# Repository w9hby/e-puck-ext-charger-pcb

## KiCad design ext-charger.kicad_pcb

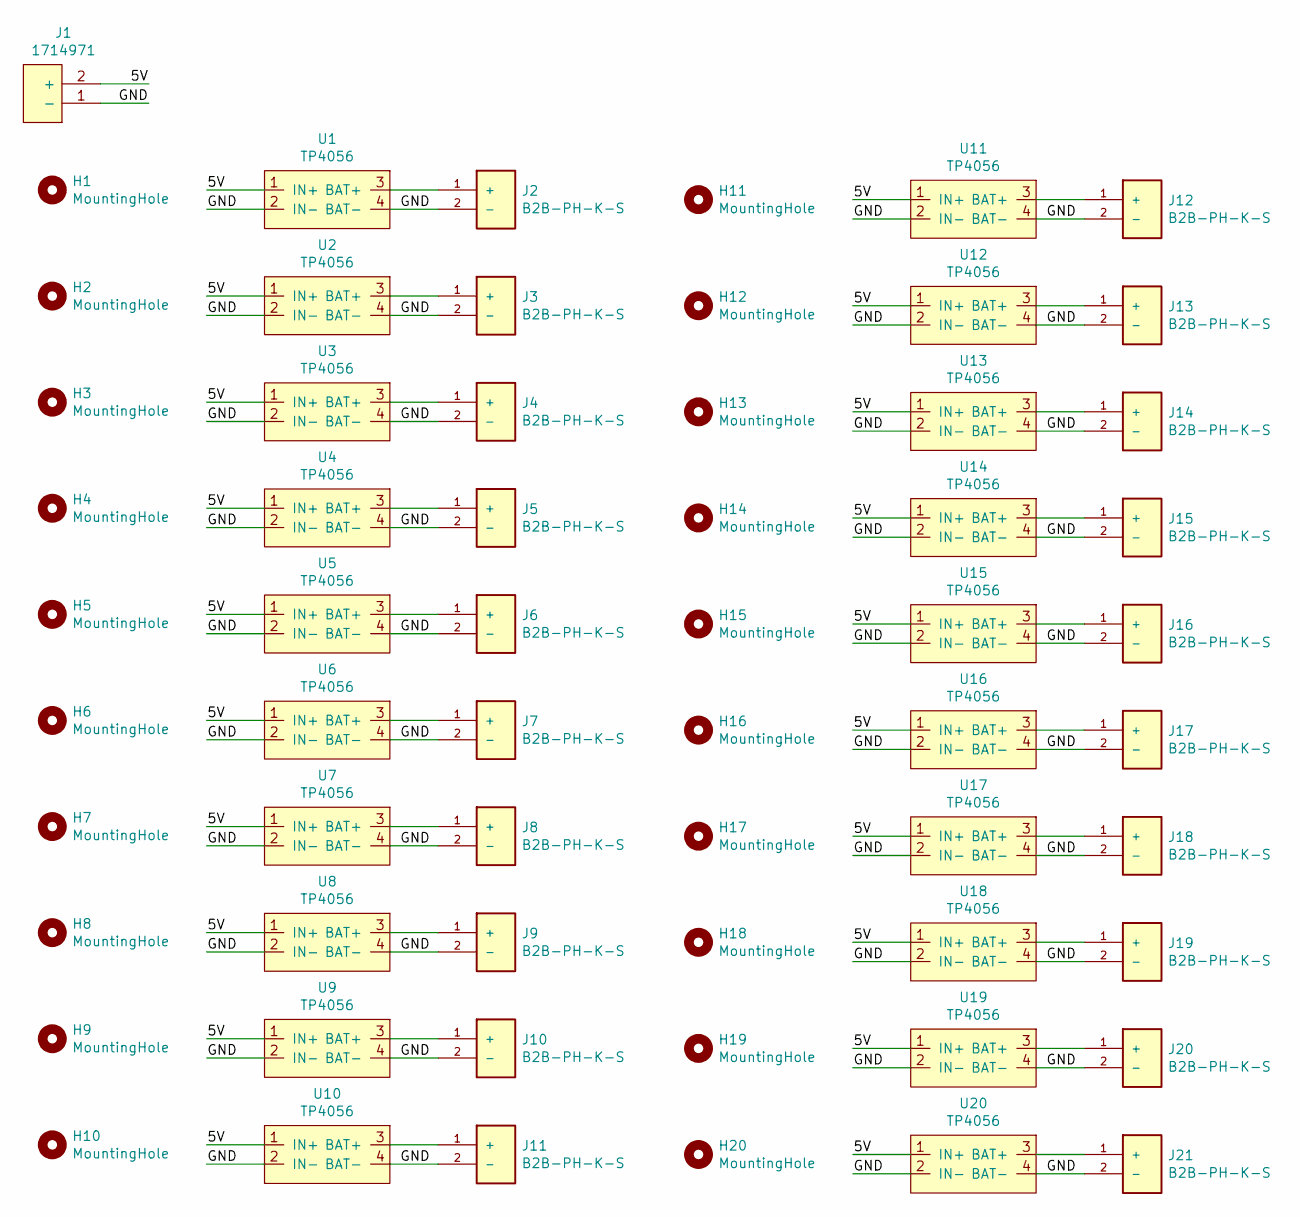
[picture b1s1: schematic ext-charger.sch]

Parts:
H1, H2, H3, H4, H5, H6, H7, H8, H9, H10, H11, H12, H13, H14, H15, H16, H17, H18, H19, H20: MountingHole; MountingHole_2.7mm_M2.5
J1: 1714971; Terminal_block
J2, J3, J4, J5, J6, J7, J8, J9, J10, J11, J12, J13, J14, J15, J16, J17, J18, J19, J20, J21: B2B-PH-K-S; JST_B2B-PH-K-S
U1, U2, U3, U4, U5, U6, U7, U8, U9, U10, U11, U12, U13, U14, U15, U16, U17, U18, U19, U20: TP4056

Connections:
/5V: J1.2 (+), U1.1 (IN+), U2.1 (IN+), U3.1 (IN+), U4.1 (IN+), U5.1 (IN+), U6.1 (IN+), U7.1 (IN+), U8.1 (IN+), U9.1 (IN+), U10.1 (IN+), U11.1 (IN+), U12.1 (IN+), U13.1 (IN+), U14.1 (IN+), U15.1 (IN+), U16.1 (IN+), U17.1 (IN+), U18.1 (IN+), U19.1 (IN+), U20.1 (IN+)
/GND: J1.1 (-), J2.2 (-), J3.2 (-), J4.2 (-), J5.2 (-), J6.2 (-), J7.2 (-), J8.2 (-), J9.2 (-), J10.2 (-), J11.2 (-), J12.2 (-), J13.2 (-), J14.2 (-), J15.2 (-), J16.2 (-), J17.2 (-), J18.2 (-), J19.2 (-), J20.2 (-), J21.2 (-), U1.2 (IN-), U1.4 (BAT-), U2.2 (IN-), U2.4 (BAT-), U3.2 (IN-), U3.4 (BAT-), U4.2 (IN-), U4.4 (BAT-), U5.2 (IN-), U5.4 (BAT-), U6.2 (IN-), U6.4 (BAT-), U7.2 (IN-), U7.4 (BAT-), U8.2 (IN-), U8.4 (BAT-), U9.2 (IN-), U9.4 (BAT-), U10.2 (IN-), U10.4 (BAT-), U11.2 (IN-), U11.4 (BAT-), U12.2 (IN-), U12.4 (BAT-), U13.2 (IN-), U13.4 (BAT-), U14.2 (IN-), U14.4 (BAT-), U15.2 (IN-), U15.4 (BAT-), U16.2 (IN-), U16.4 (BAT-), U17.2 (IN-), U17.4 (BAT-), U18.2 (IN-), U18.4 (BAT-), U19.2 (IN-), U19.4 (BAT-), U20.2 (IN-), U20.4 (BAT-)
unnamed: J2.1 (+), U1.3 (BAT+)
unnamed: J3.1 (+), U2.3 (BAT+)
unnamed: J4.1 (+), U3.3 (BAT+)
unnamed: J5.1 (+), U4.3 (BAT+)
unnamed: J6.1 (+), U5.3 (BAT+)
unnamed: J7.1 (+), U6.3 (BAT+)
unnamed: J8.1 (+), U7.3 (BAT+)
unnamed: J9.1 (+), U8.3 (BAT+)
unnamed: J10.1 (+), U9.3 (BAT+)
unnamed: J11.1 (+), U10.3 (BAT+)
unnamed: J12.1 (+), U11.3 (BAT+)
unnamed: J13.1 (+), U12.3 (BAT+)
unnamed: J14.1 (+), U13.3 (BAT+)
unnamed: J15.1 (+), U14.3 (BAT+)
unnamed: J16.1 (+), U15.3 (BAT+)
unnamed: J17.1 (+), U16.3 (BAT+)
unnamed: J18.1 (+), U17.3 (BAT+)
unnamed: J19.1 (+), U18.3 (BAT+)
unnamed: J20.1 (+), U19.3 (BAT+)
unnamed: J21.1 (+), U20.3 (BAT+)

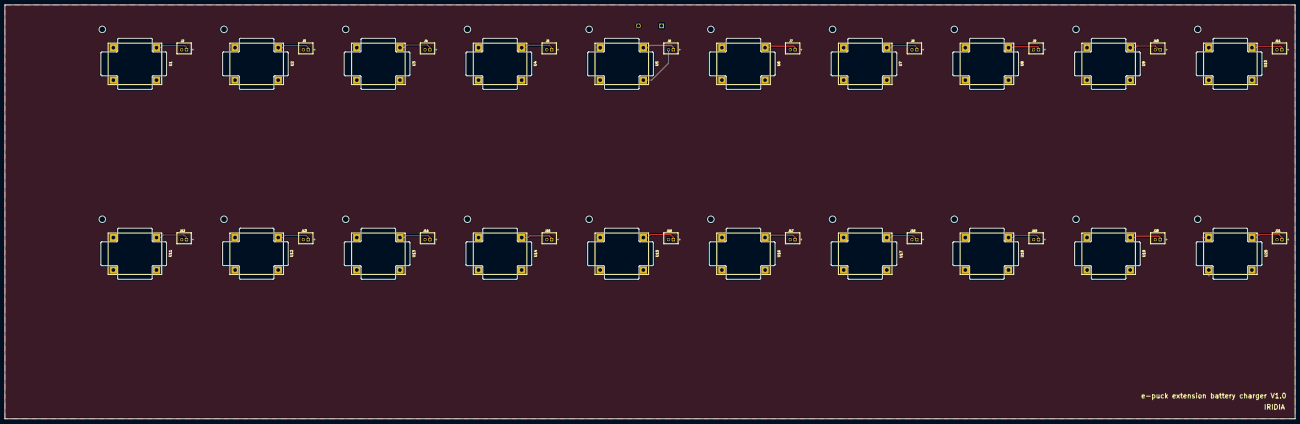
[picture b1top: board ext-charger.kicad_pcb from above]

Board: 2 copper layers, 530.0 x 170.0 mm, 61 parts (1 on the bottom side), 22 nets.

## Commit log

2020-03-16 project init
2020-03-16 copied symbols and footprints from e-puck-charger
2020-03-17 created the schematic
2020-03-17 finished component placement
2020-03-17 finished routing
2020-03-21 added filled zones
